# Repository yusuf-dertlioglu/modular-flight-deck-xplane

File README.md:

# Modular Embedded Flight Deck (X-Plane 11)

A modular desktop flight simulator cockpit for X-Plane 11, built around a Raspberry Pi Pico (RP2040), LVGL, and 4 custom KiCad PCBs, with an experimental v2.0-beta architecture upgrading the display to a capacitive ESP32-S3 IPS touch module and splitting Wi-Fi telemetry from real-time USB HID controls.

Flight Demo (Takeoff & Climb): [Watch on YouTube](https://youtu.be/x1ZjBMRiYiw?si=wxdTexv7rL8de2k_)

---

## System Overview

In v1.0, the system consists of a central controller board and three modular satellite boards connected via cables:

- Central Board: Raspberry Pi Pico (RP2040) running firmware written in C (Pico SDK), driving a resistive TFT touch display with LVGL for live telemetry and autopilot state/target display, paired with a rotary encoder for adjusting autopilot target values.
- Left Satellite Board: Dual sliders for Throttle and Mixture, a horizontal slider for Rudder, and an ergonomically placed brake toggle pushbutton right next to the rudder slider for simultaneous braking and steering during taxi/landing.
- Right Satellite Board: Compact 2-axis industrial joystick adapted as the primary pitch/roll flight input.
- Center Satellite Board: Mini-joystick for camera control, 2 buttons for camera zoom in/out, 2 assignable buttons (intended for left/right toe brakes; mapped to Battery & Avionics in the demo video), 2 toggle switches for Landing Gear and Parking Brake, and a 2-way (MOM)-OFF-(MOM) toggle switch for Flaps Up/Down.

### Communication & Simulator Bridge (v1.0)

- Flight Controls: Transmitted from the RP2040 via native USB HID.
- Telemetry & Autopilot Sync: Bidirectional exchange over USB CDC and a custom Python UDP bridge communicating with X-Plane 11.

Detailed Documentation:
- [System Architecture v1.0](docs/architecture-v1.md)
- [Hardware Bring-Up & Rework Notes (v0.9)](docs/hardware-rework-v0.9.md)
- [v2.0-beta Architecture, Wired Prototype Plan & Testing](docs/architecture-v2-outlook.md)

---

## Versions & Status

- v1.0 (Active) — Hardware: `pcb-v0.9` (with rework) + satellite PCBs | Software: `rp2040-v1` (HID + CDC) & Python UDP bridge | Status: Working & in use.
- PCB Rev 1.0 — Hardware: `pcb-v1.0-revised` (mainboard + 2 revised satellites) | Software: Compatible with `rp2040-v1` | Status: KiCad layout updated (not ordered).
- v2.0-beta (Outlook) — Hardware: `pcb-v0.9` wired to ESP32-S3 IPS display | Software: `rp2040-v2-hid-only` + `esp32-s3-v2-display` | Status: Experimental / wired test planned (no new PCB spin).

### Motivation for v2.0-beta

The primary driver for v2.0-beta is display ergonomics and usability: the current TFT display suffers from strong color inversion/distortion when viewed at an angle from a seated desk position, and its resistive touch layer requires firm pressure. Upgrading to an ESP32-S3 integrated capacitive IPS LCD solves both issues while naturally offloading Wi-Fi UDP telemetry and LVGL UI rendering from the RP2040—leaving the RP2040 dedicated solely to deterministic real-time I/O and native USB HID (creating headroom for future input filtering and features). For initial testing, the ESP32-S3 module will be wired directly to the existing `pcb-v0.9` mainboard.

---

## Hardware Bring-Up & Lessons Learned (v0.9 -> v1.0)

Bringing up the manufactured `pcb-v0.9` boards (KiCad, fabricated via JLCPCB) revealed two layout mistakes that were reworked directly on the hardware and fixed in `pcb-v1.0-revised` (see [docs/hardware-rework-v0.9.md](docs/hardware-rework-v0.9.md)):

- DIP-16 footprint too wide (2 satellite PCBs): Mounted DIP-16 sockets onto the PCBs via small perfboard adapters during bring-up; corrected the DIP-16 footprint in `pcb-v1.0-revised`.
- Swapped rotary encoder pinout (Central board): Cut traces and rerouted two pins using magnet/coil wire (`bodge wires`) during bring-up; fixed schematic pinout and PCB routing in `pcb-v1.0-revised`.
- Incorrect mounting geometry on `Flightstick_Top` PCB: Used a 3D-printed mounting plate as a workaround to mount the flight stick in `v0.9`; fixed the board geometry in `pcb-v1.0-revised`.

---

## Possible Future Extensions

- HUD-Style Display Layout: Replacing boxed numeric telemetry readouts with an aviation-style artificial horizon / HUD layout in LVGL.
- Camera Joystick Smoothing Filter: Adding a digital low-pass / exponential moving average filter on the RP2040 to eliminate jitter when deflecting the mini-joystick from its center deadzone.
- Angled Display Mount via Minimal Wiring: On a dedicated `v2.0` central PCB, the ESP32-S3 display only requires two 4-pin connectors (1x UART + 1x Rotary Encoder), making it easy to mount the display at an ergonomic viewing angle using a simple mechanical spacer/bracket.

---

## Repository Structure

```text
.
├── README.md
├── docs/
│   ├── hardware-rework-v0.9.md      # Bring-up issues, rework notes & photos
│   ├── architecture-v1.md           # Current v1.0 hardware & software architecture
│   └── architecture-v2-outlook.md   # v2.0-beta split architecture & wired v0.9 test notes
├── hardware/
│   ├── pcb-v0.9-manufactured/       # KiCad files for manufactured v0.9 boards
│   └── pcb-v1.0-revised/            # Revised KiCad files (unmanufactured bugfix revision)
├── firmware/
│   ├── rp2040-v1/                   # C / Pico SDK firmware (I/O, LVGL, USB HID + CDC)
│   ├── rp2040-v2-hid-only/          # Planned lean RP2040 firmware (HID & controls only)
│   └── esp32-s3-v2-display/         # Planned ESP32-S3 firmware (Wi-Fi UDP & LVGL UI)
├── bridge/
│   ├── xplane_bridge.py             # Python UDP bridge for X-Plane 11
│   └── XPlane_Setup.md              # Setup for X-Plane 11
└── media/                           # Photos, diagrams & hardware rework documentation

```

## Development Notes & AI Assistance

Hardware design, PCB bring-up, physical rework, wiring, and system testing were carried out hands-on. AI tools were used as development assistants during the project: Claude Sonnet was primarily used to help draft firmware code, while Gemini was used to help structure the project plan, debug code issues, and iterate on the display UI.

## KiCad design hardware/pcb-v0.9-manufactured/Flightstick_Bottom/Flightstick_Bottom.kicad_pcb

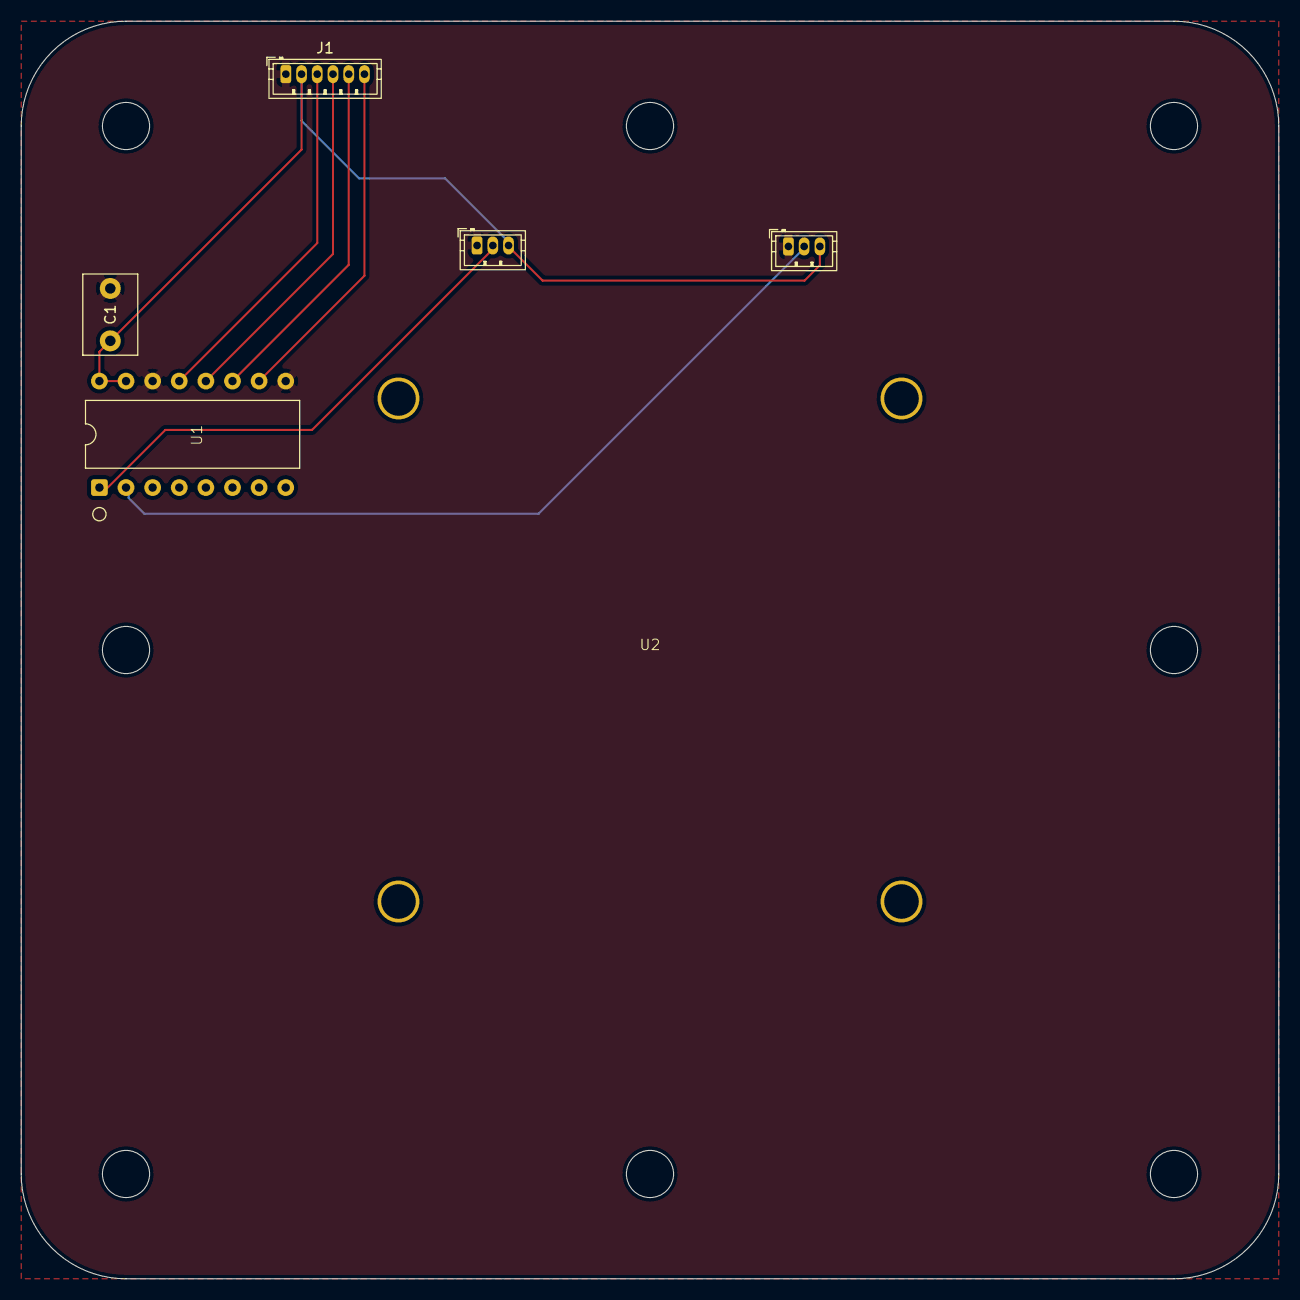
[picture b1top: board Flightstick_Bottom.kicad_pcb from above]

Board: 2 copper layers, 120.0 x 120.0 mm, 4 parts (0 on the bottom side), 8 nets.

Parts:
C1: 100n; C_Disc_D7.5mm_W5.0mm_P5.00mm
J1: JST_ZH_B6B-ZR_1x06_P1.50mm_Vertical
U1: MCP3208; DIP-16_Custom
U2: Flightstick; Joystick_Bottom

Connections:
+3V3: C1.1, J1.2 (VCC), U1.15 (Vref), U1.16 (Vdd), U2.3 (VCC), U2.6 (VCC)
GND: C1.2, J1.1 (GND), U1.9 (DGND), U1.14 (AGND), U2.1 (GND), U2.4 (GND)
unnamed: J1.3 (CLK), U1.13 (CLK)
unnamed: J1.6 (CS), U1.10 (~CS/SHDN)
unnamed: J1.4 (MISO), U1.12 (Dout)
unnamed: J1.5 (MOSI), U1.11 (Din)
unnamed: U1.1 (CH0), U2.2 (x)
unnamed: U1.2 (CH1), U2.5 (y)

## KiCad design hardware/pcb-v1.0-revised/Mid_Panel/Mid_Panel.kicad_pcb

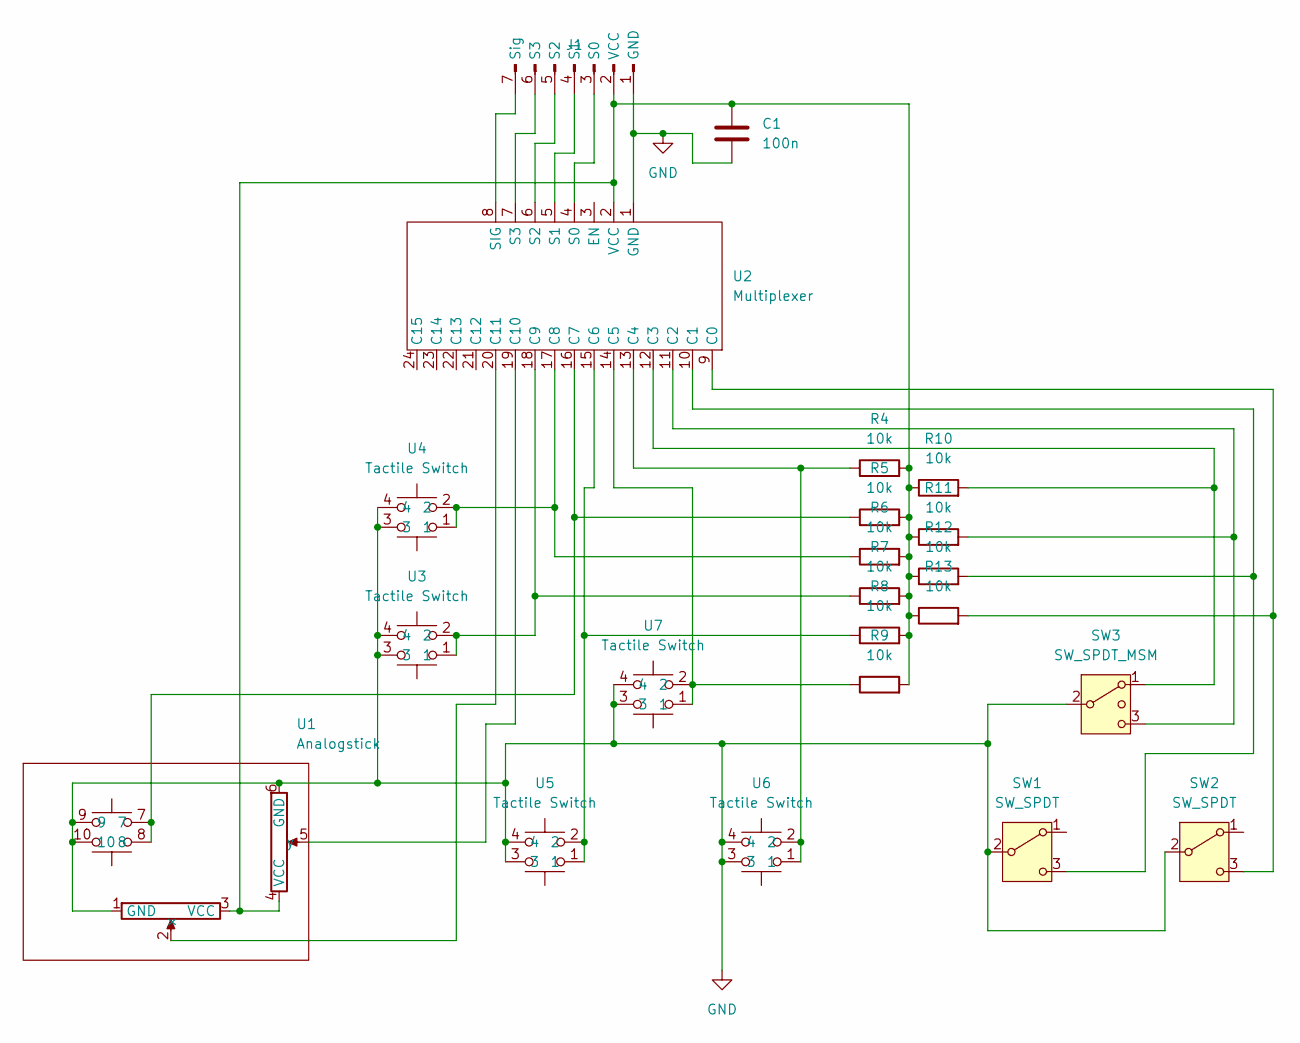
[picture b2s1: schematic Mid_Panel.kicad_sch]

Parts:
C1: 100n; C_Disc_D10.5mm_W5.0mm_P5.00mm
J1: JST_ZH_B7B-ZR_1x07_P1.50mm_Vertical
R4, R5, R6, R7, R8, R9, R10, R11, R12, R13: 10k; R_Axial_DIN0207_L6.3mm_D2.5mm_P10.16mm_Horizontal
SW1, SW2: SW_SPDT; Switch_On_On
SW3: SW_SPDT_MSM; Switch_MOM_OFF_MOM
U1: Analogstick; TMR_Stick
U2: Multiplexer
U3, U4, U5, U6, U7: Tactile Switch; Tactile_Switch

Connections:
GND: C1.2, J1.1 (GND), SW1.2 (B), SW2.2 (B), SW3.2 (3), U1.1 (GND), U1.6 (GND), U1.9, U1.10, U2.1 (GND), U3.3, U3.4, U4.3, U4.4, U5.3, U5.4, U6.3, U6.4, U7.3, U7.4
unnamed: J1.3 (S0), U2.4 (S0)
unnamed: J1.4 (S1), U2.5 (S1)
unnamed: J1.5 (S2), U2.6 (S2)
unnamed: J1.6 (S3), U2.7 (S3)
unnamed: J1.7 (Sig), U2.8 (SIG)
unnamed: C1.1, J1.2 (VCC), R4.2, R5.2, R6.2, R7.2, R8.2, R9.2, R10.1, R11.1, R12.1, R13.1, U1.3 (VCC), U1.4 (VCC), U2.2 (VCC)
unnamed: R12.2, SW1.3 (C), U2.10 (C1)
unnamed: R13.2, SW2.3 (C), U2.9 (C0)
unnamed: R11.2, SW3.3 (4), U2.11 (C2)
unnamed: U1.2 (x), U2.20 (C11)
unnamed: U1.5 (y), U2.19 (C10)
unnamed: R10.2, SW3.1, U2.12 (C3)
unnamed: R4.1, U2.13 (C4), U6.1, U6.2
unnamed: R9.1, U2.14 (C5), U7.1, U7.2
unnamed: R8.1, U2.15 (C6), U5.1, U5.2
unnamed: R5.1, U1.7, U1.8, U2.16 (C7)
unnamed: R6.1, U2.17 (C8), U4.1, U4.2
unnamed: R7.1, U2.18 (C9), U3.1, U3.2

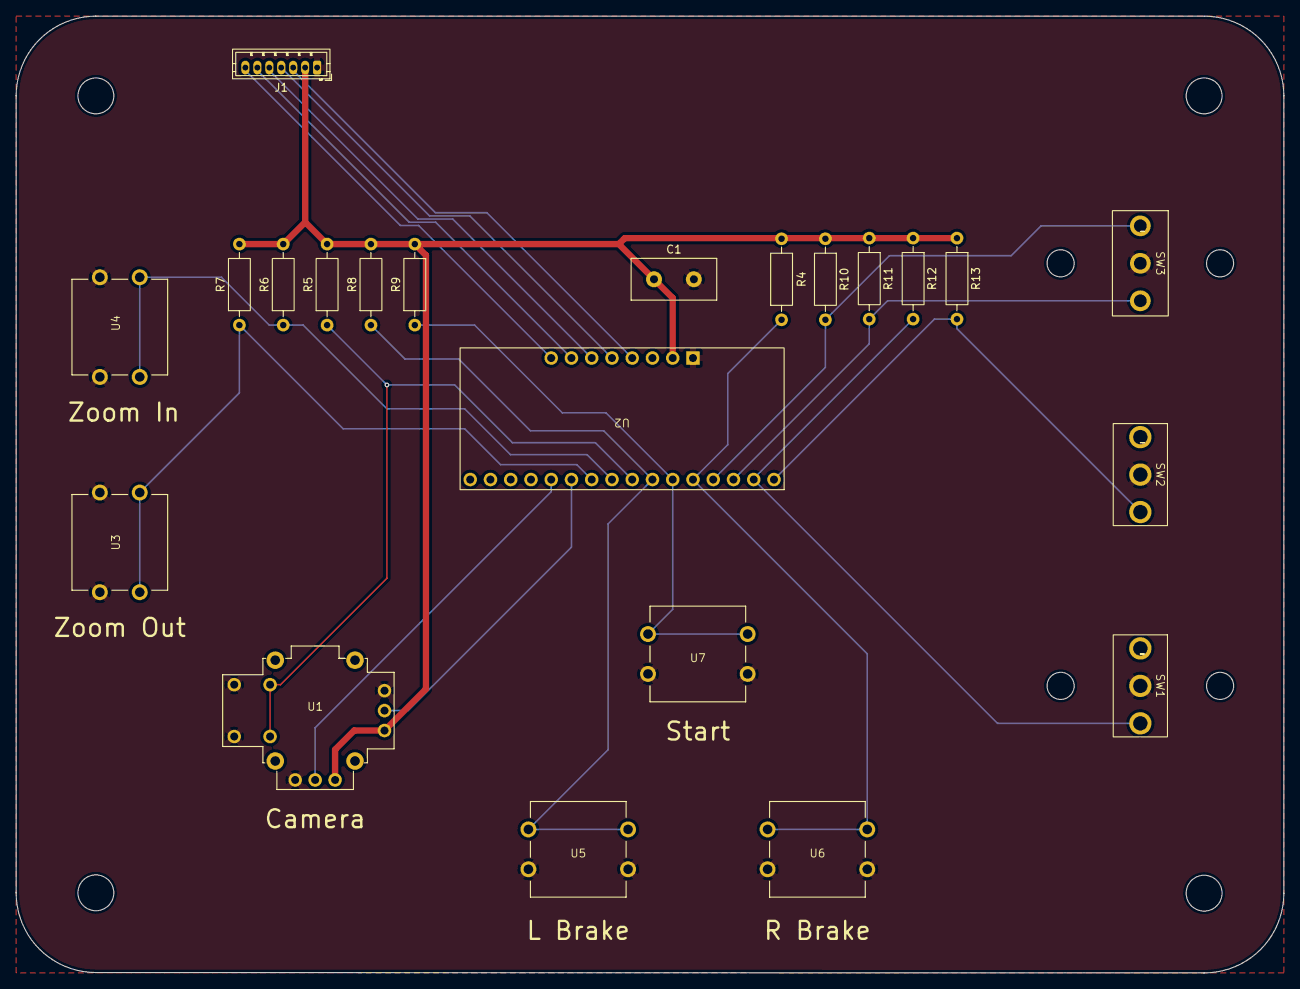
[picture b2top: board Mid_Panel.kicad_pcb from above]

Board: 2 copper layers, 159.0 x 120.0 mm, 22 parts (0 on the bottom side), 19 nets.

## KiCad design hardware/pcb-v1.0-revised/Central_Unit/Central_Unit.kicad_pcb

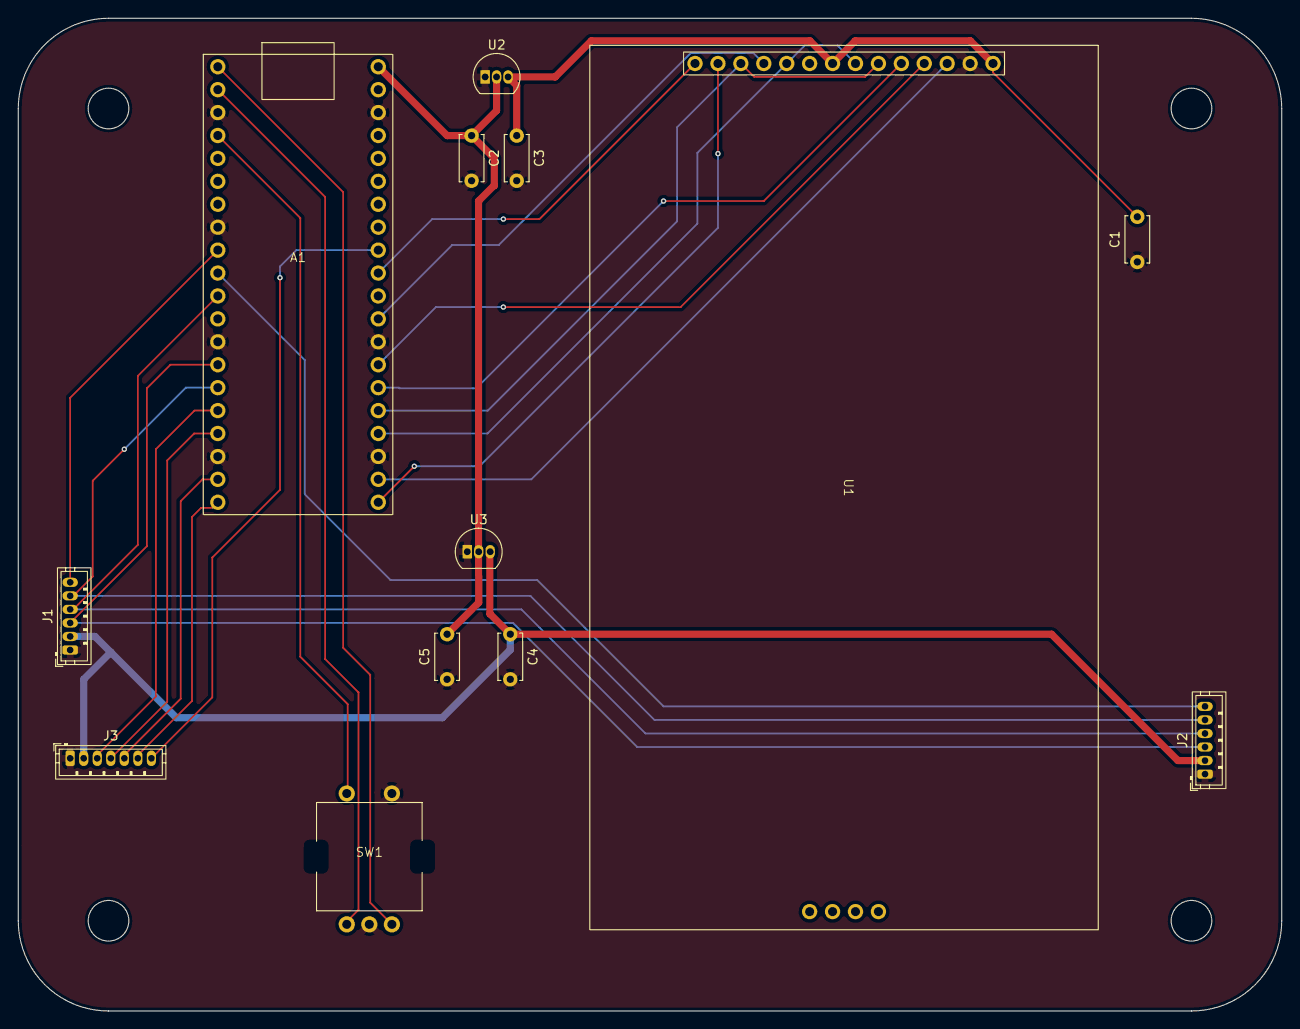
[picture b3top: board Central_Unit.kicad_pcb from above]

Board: 2 copper layers, 140.0 x 110.0 mm, 13 parts (0 on the bottom side), 25 nets.

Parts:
A1: RaspberryPi_Pico; Raspberry_Pi_Pico
C1, C2, C3, C4, C5: 10u; C_Disc_D5.0mm_W2.5mm_P5.00mm
J1, J2: JST_ZH_B6B-ZR_1x06_P1.50mm_Vertical
J3: JST_ZH_B7B-ZR_1x07_P1.50mm_Vertical
SW1: RotaryEncoder_Switch; Encoder
U1: 3.5" SPI TFT Touch Display; 3.5_TFT_Display
U2, U3: HT73333 LDO; TO-92_Inline

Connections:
/ADC1: A1.32 (GPIO27_ADC1), J3.7 (Sig)
GND: A1.3 (GND), A1.8 (GND), A1.13 (GND), A1.18 (GND), A1.23 (GND), A1.28 (GND), A1.38 (GND), C1.1, C2.2, C3.2, C4.2, C5.2, J1.1 (GND), J2.1 (GND), J3.1 (GND), SW1.C, SW1.S2, U1.2 (GND), U2.1 (GND), U3.1 (GND)
unnamed: A1.1 (GPIO0), SW1.B
unnamed: A1.2 (GPIO1), SW1.A
unnamed: A1.4 (GPIO2), SW1.S1
unnamed: A1.9 (GPIO6), J1.6 (CS)
unnamed: A1.10 (GPIO7), J2.6 (CS)
unnamed: A1.11 (GPIO8), J1.4 (MISO), J2.4 (MISO)
unnamed: A1.14 (GPIO10), J1.3 (CLK), J2.3 (CLK)
unnamed: A1.15 (GPIO11), J1.5 (MOSI), J2.5 (MOSI)
unnamed: A1.16 (GPIO12), J3.3 (S0)
unnamed: A1.17 (GPIO13), J3.4 (S1)
unnamed: A1.19 (GPIO14), J3.5 (S2)
unnamed: A1.20 (GPIO15), J3.6 (S3)
unnamed: A1.21 (GPIO16), U1.13 (T_OUT)
unnamed: A1.22 (GPIO17), U1.3 (CS)
unnamed: A1.24 (GPIO18), U1.7 (SCK), U1.10 (T_CLK)
unnamed: A1.25 (GPIO19), U1.6 (SDI), U1.12 (T_DIN)
unnamed: A1.26 (GPIO20), U1.5 (D/C)
unnamed: A1.27 (GPIO21), U1.4 (RST)
unnamed: A1.29 (GPIO22), U1.11 (T_CS)
unnamed: A1.31 (GPIO26_ADC0), U1.14 (T_IRQ)
unnamed: A1.40 (VBUS), C2.1, C5.1, U2.2 (V_In), U3.2 (V_In)
unnamed: C4.1, J1.2 (VCC), J2.2 (VCC), J3.2 (VCC), U3.3 (V_Out)
unnamed: C1.2, C3.1, U1.1 (VCC), U1.8 (LED), U2.3 (V_Out)
